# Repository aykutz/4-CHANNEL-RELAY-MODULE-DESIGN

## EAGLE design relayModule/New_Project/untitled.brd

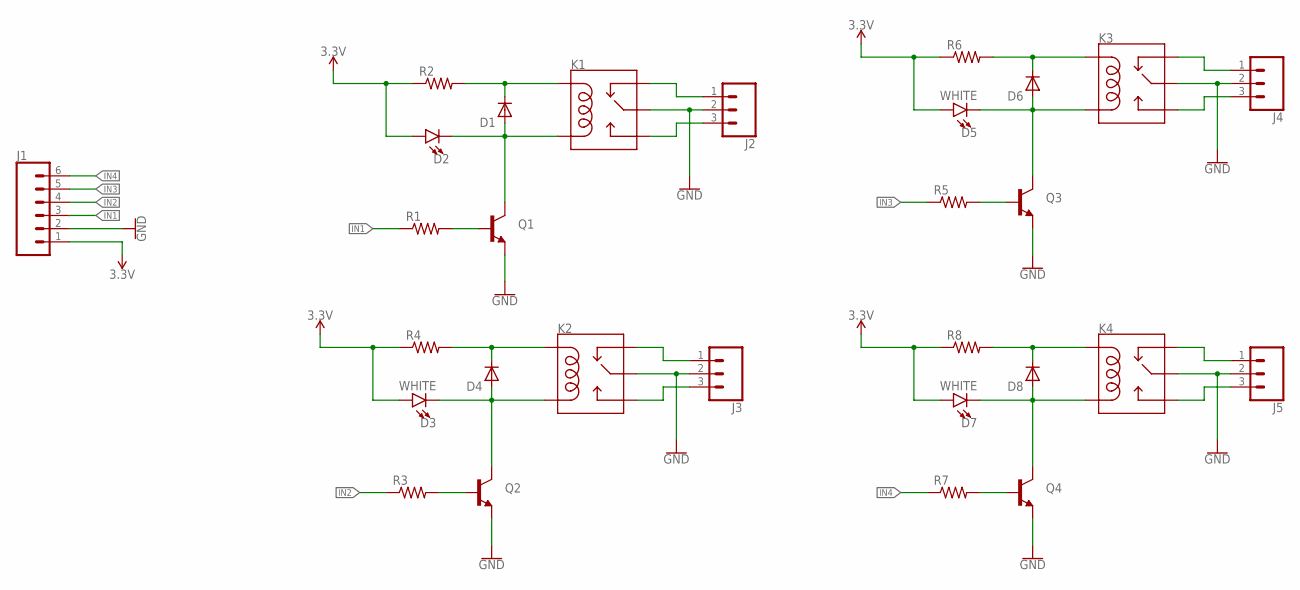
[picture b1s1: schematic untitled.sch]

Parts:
D1, D4, D6, D8: DIODE-SOD123; SOD123
D2: LED-WHITE1206; LED-1206
D3, D5, D7: WHITE; LED-1206
J1: CONN_06SILK_FEMALE_PTH; 1X06
J2, J3, J4, J5: CONN_03-SCREW-5MM; SCREWTERMINAL-5MM-3
K1, K2, K3, K4: RELAY-SPDT; RELAY_G5LE
Q1, Q2, Q3, Q4: TRANSISTOR_NPNSOT89; SOT89
R1, R2, R3, R4, R5, R6, R7, R8: RESISTOR1206; 1206

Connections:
3.3V: D2.A, D3.A, D5.A, D7.A, J1.1, R2.1, R4.1, R6.1, R8.1
GND: J1.2, J2.2, J3.2, J4.2, J5.2, K1.1 (MAIN), K2.1 (MAIN), K3.1 (MAIN), K4.1 (MAIN), Q1.3 (E), Q2.3 (E), Q3.3 (E), Q4.3 (E)
IN1: J1.3, R1.1
IN2: J1.4, R3.1
IN3: J1.5, R5.1
IN4: J1.6, R7.1
unnamed: D1.C, K1.2 (COIL1), R2.2
unnamed: D1.A, D2.C, K1.5 (COIL2), Q1.2 (C)
unnamed: Q1.1 (B), R1.2
unnamed: D4.C, K2.2 (COIL1), R4.2
unnamed: J2.3, K1.3 (NO)
unnamed: D3.C, D4.A, K2.5 (COIL2), Q2.2 (C)
unnamed: J2.1, K1.4 (NC)
unnamed: Q2.1 (B), R3.2
unnamed: J3.3, K2.3 (NO)
unnamed: J3.1, K2.4 (NC)
unnamed: D6.C, K3.2 (COIL1), R6.2
unnamed: D5.C, D6.A, K3.5 (COIL2), Q3.2 (C)
unnamed: Q3.1 (B), R5.2
unnamed: J4.3, K3.3 (NO)
unnamed: J4.1, K3.4 (NC)
unnamed: D8.C, K4.2 (COIL1), R8.2
unnamed: D7.C, D8.A, K4.5 (COIL2), Q4.2 (C)
unnamed: Q4.1 (B), R7.2
unnamed: J5.3, K4.3 (NO)
unnamed: J5.1, K4.4 (NC)

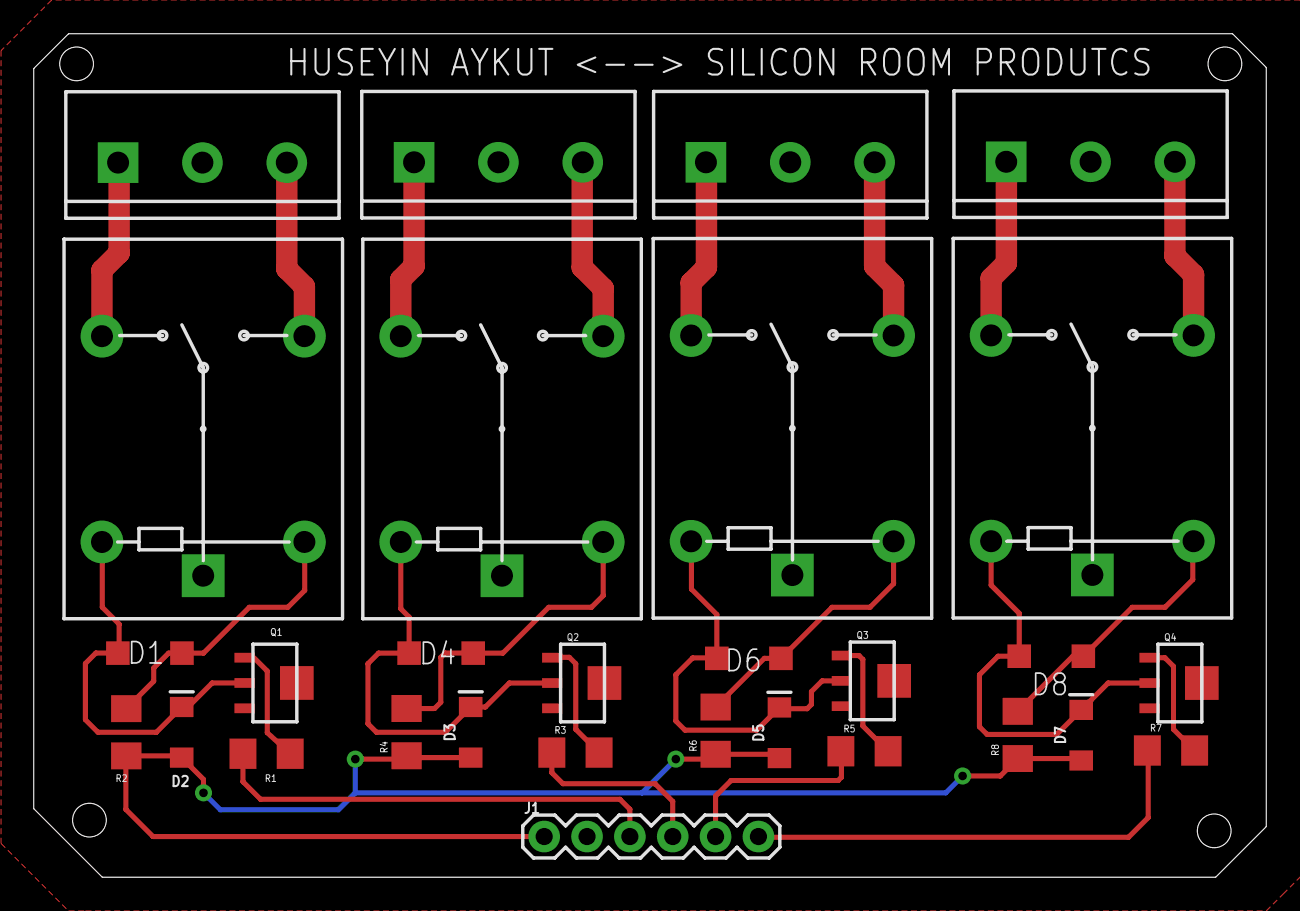
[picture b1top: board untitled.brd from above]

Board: 2 copper layers, 73.1 x 50.0 mm, 29 parts (0 on the bottom side), 26 nets.

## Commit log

2024-09-15 4 CHANNEL RELAY MODULE DESIGN

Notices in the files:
parts and their libraries:
SparkFun-LED: Licensing: Creative Commons ShareAlike 4.0 International - https://creativecommons.org/licenses/by-sa/4.0
